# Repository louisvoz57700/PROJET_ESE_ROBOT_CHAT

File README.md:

# 🤖 PROJET_ESE_ROBOT_CHAT

Bienvenue dans le repository de notre projet de 3ème année.  
Ce projet a pour but de concevoir et développer un **robot intelligent** capable d’interagir et d’échanger de manière autonome dans le cadre du jeu "Chat".  

---

## 👥 Membres de l’équipe

- [Louis Vozzola](https://github.com/louisvoz57700)  
- [Antoine LEMARIGNIER](https://github.com/LEMARIGNIER-Antoine)  
- [Thomas TERLINDEN](https://github.com/TTrld)
- [Kenny Saint Fleur](https://github.com/Kennystflr)  

---

## 📁 Structure du projet

Ce dépôt est organisé de la manière suivante :

- `Datasheet/` : Contient les **documents techniques** des composants électroniques (datasheets, notes d’application, documents de référence).  

- `Hardware/` : Contient la **conception matérielle**, incluant les projets KiCad (schémas, PCB, librairies locales) et fichiers liés à la fabrication (impression 3D).  

- `IMG/` : Contient toutes les **images et illustrations** du projet (schémas explicatifs, rendus PCB, photos du prototype, captures pour la documentation).  

- `Software/` : Contient le **code source / firmware**, y compris les projets STM32CubeIDE, le code embarqué (C/C++) et les scripts utilitaires éventuels.

---

## 📅 Organisation

- **Phase 1 (Début Septembre)** : Étude et conception
Nous avons étudié les possibilités et choisis d'adopter [deux solutions de pcb](./Hardware).
- **Phase 2 (Mi-Septembre à Mi-Octobre)** : Développement hardware & software
Nous avons réalisé le developpement hardware du projet en 3 semaines et nous avons ensuite concentré nos efforts sur le développement des blocks individuels du software embarqué.
- **Phase 3 (Décembre)** : Intégration et tests
Nous avons intégrés et adaptés les différents blocks des capteurs et actionneurs dans le [code résultant](./Software). 
- **Phase 4  (Janvier)** : Présentation finale
Malgré le dépqart en double-dipplome de la majorité de l'équipe, nous avons travaillé a obtenir des extraits vidéos montrant le résultat de nos travaux.  

---

## 🛠️ Technologies utilisées (prévisionnel)

- **Langages** : Python / C  
- **Matériel** : STM32 / VL053 / LIDAR
- **Fabrication** : JLCPCB / Imprimante 3D FDM / Fusion 360

---
## Résultats :

### Vidéo finale du chat en jeu :
https://github.com/user-attachments/assets/e0ab9da4-8b44-4d55-9d14-98a5d518202f

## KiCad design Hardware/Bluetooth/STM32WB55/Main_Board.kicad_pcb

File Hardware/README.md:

# 🛠️ Hardware – README

Bienvenue dans ce README dédié à **l’ensemble de la partie hardware** du projet.

---

## 🧩 Architecture matérielle

Pour notre projet, nous avons conçu **deux PCB distincts**, chacun répondant à un objectif précis :

- **[Bluetooth WB55](./WB55)**  
  Carte principale intégrant le microcontrôleur **STM32WB55** et l’ensemble de la chaîne Bluetooth Low Energy.

- **[Mainboard G431](./G431)**  
  Carte secondaire conçue comme solution de secours, destinée à prendre le relais en cas de défaillance du PCB Bluetooth.

Notre stratégie de développement s’est appuyée sur la conception d’un **module Bluetooth dédié**, incluant les éléments les plus critiques du design RF, notamment l’antenne et ses réseaux d’adaptation.  
En parallèle, par souci de robustesse et de gestion des risques, une **Mainboard alternative** a été développée pour garantir la continuité du projet.

Le module Bluetooth s’étant révélé **fonctionnel et performant dès la première mise sous tension**, nous avons validé cette architecture et décidé de **ne pas retenir la solution de repli** basée sur la Mainboard.

---

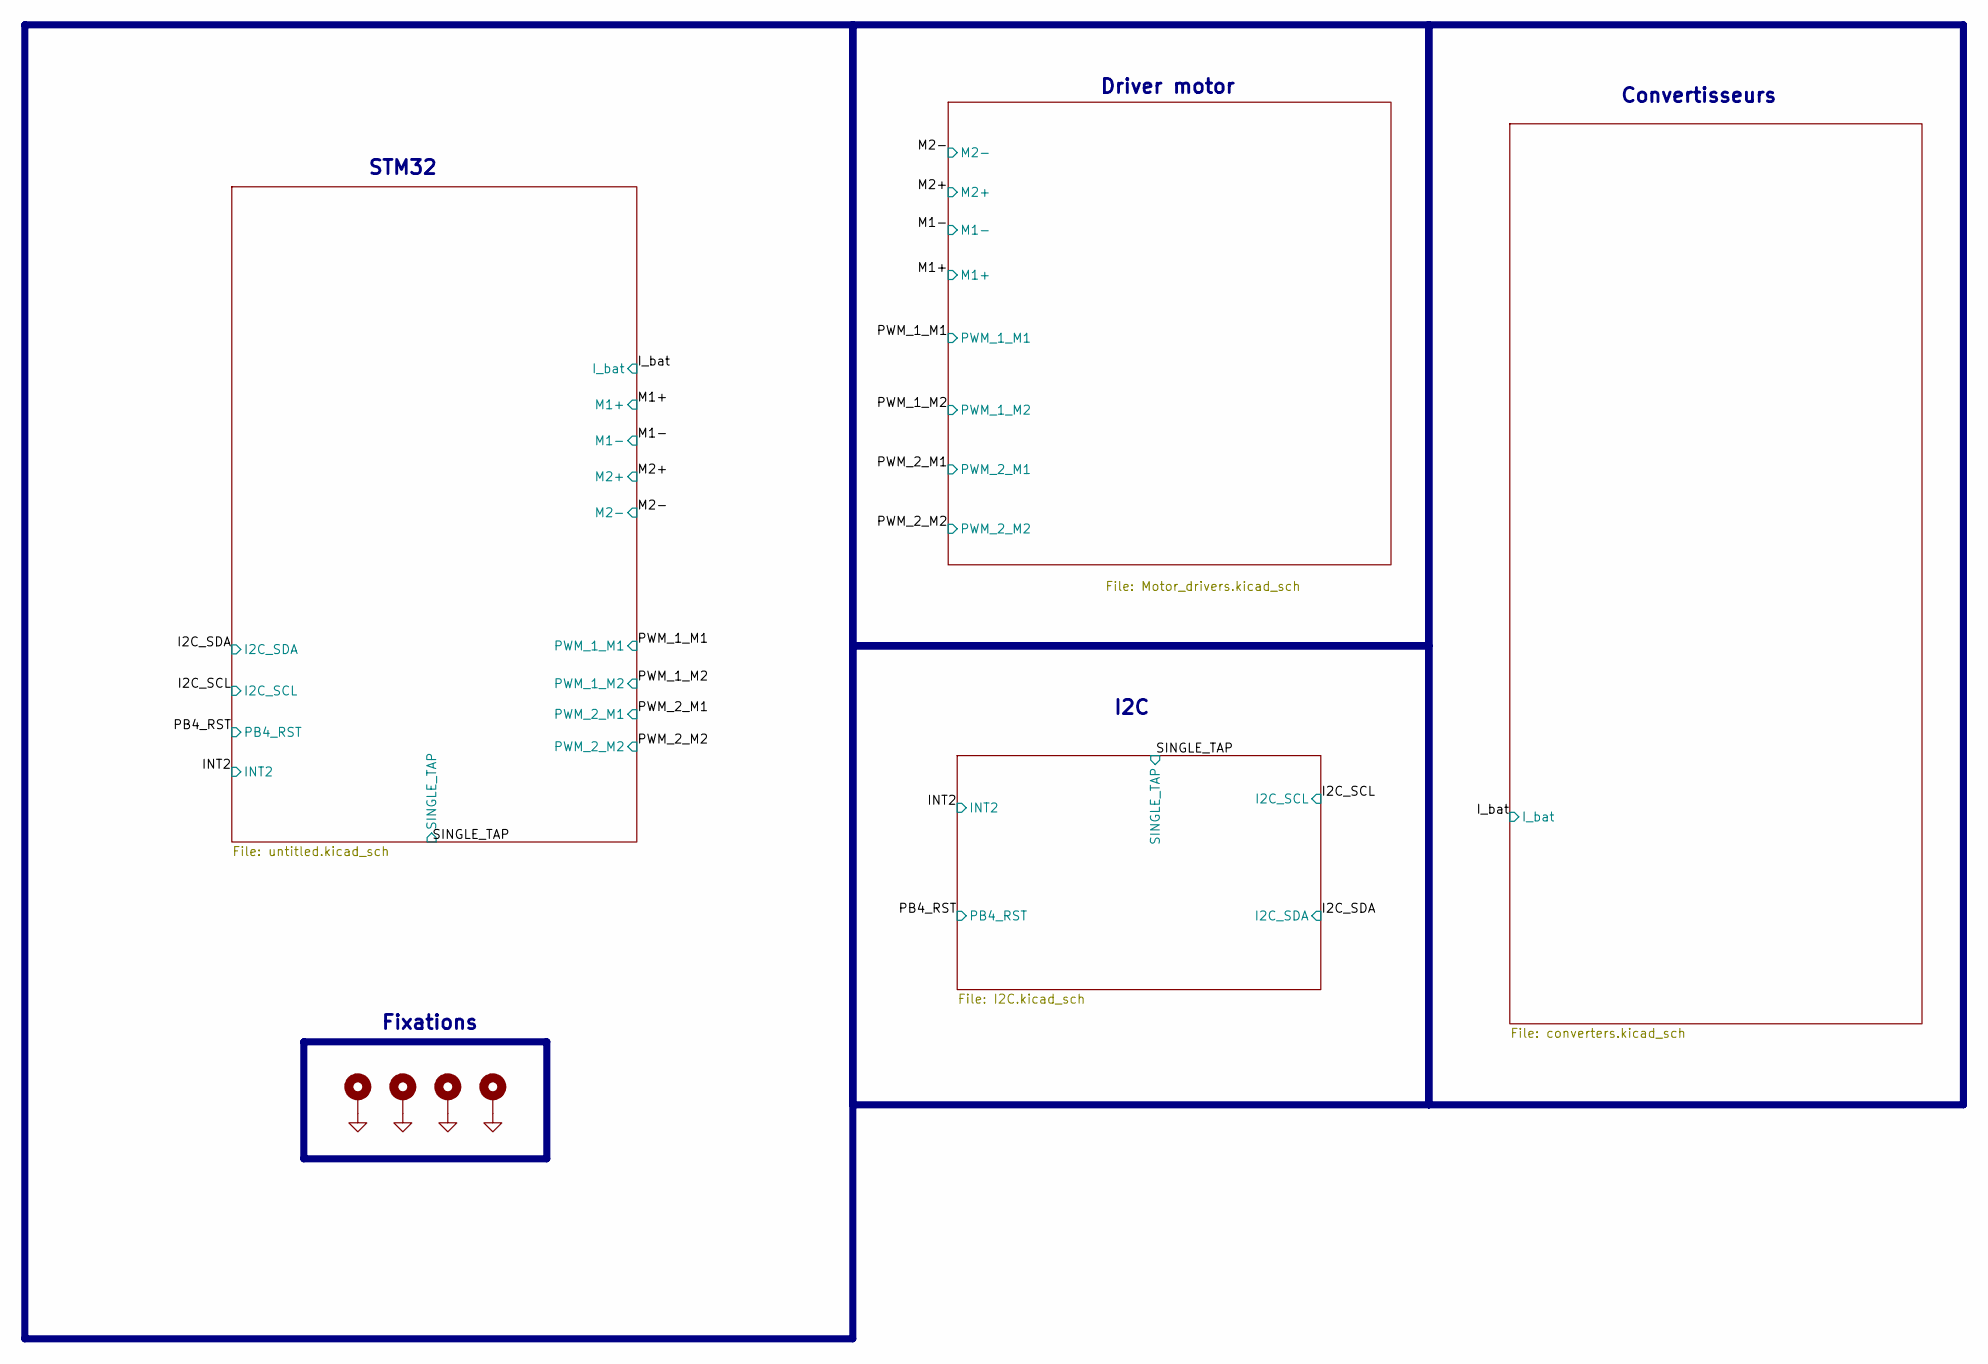
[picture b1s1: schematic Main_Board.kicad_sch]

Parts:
H1, H2, H3, H4: MountingHole_Pad; MountingHole_3.2mm_M3_Pad_Via

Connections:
GND: H1.1, H2.1, H3.1, H4.1; also elsewhere on the board

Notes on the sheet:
Convertisseurs
I2C
STM32
Fixations
Driver motor

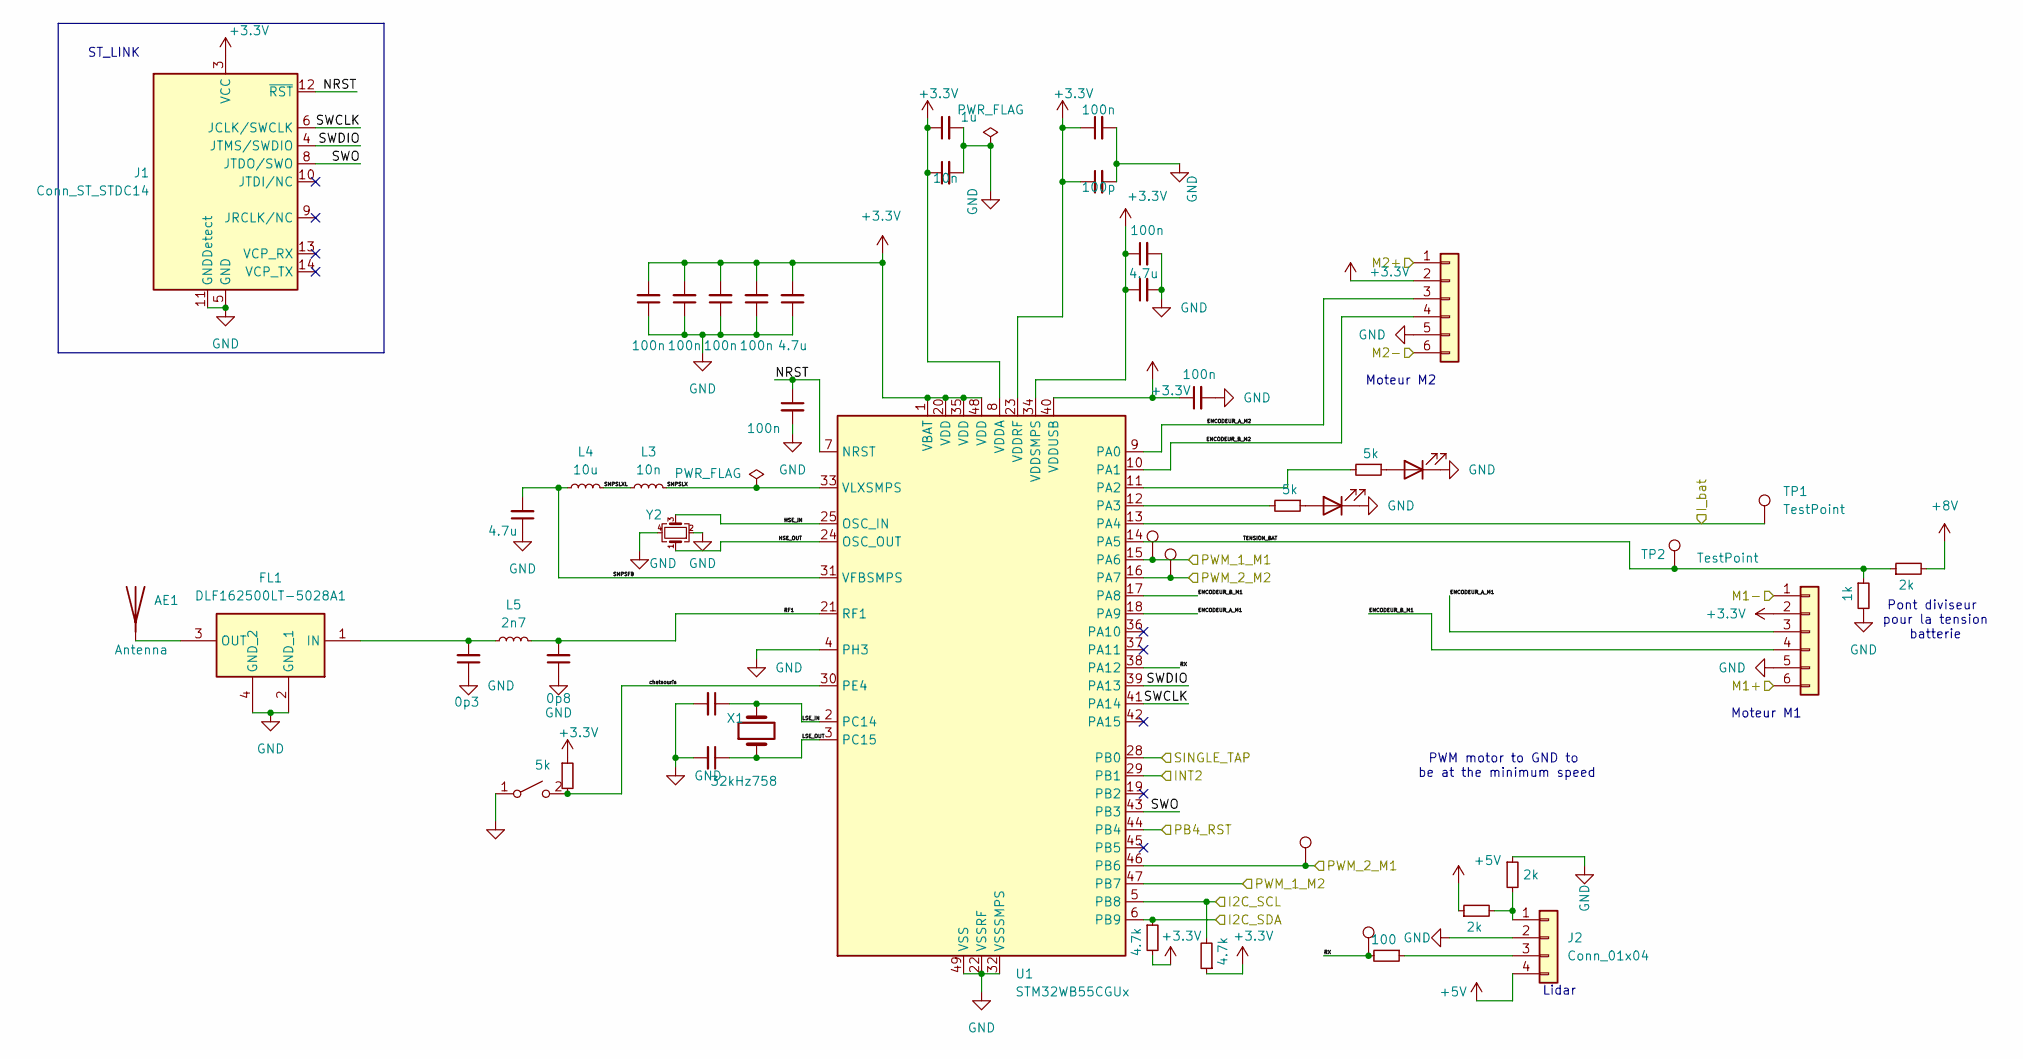
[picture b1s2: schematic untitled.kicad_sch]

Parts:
AE1: Antenna; 2.4GHz BLE
C1: 10n; C_0402_1005Metric
C2: 1u; C_0402_1005Metric
C5, C6, C7, C8, C9, C11, C38: 100n; C_0603_1608Metric
C10: 100p; C_0603_1608Metric
C12, C39, C43: 4.7u; C_0603_1608Metric
C13, C14: 13p; C_0402_1005Metric
C40: 0p3; C_0402_1005Metric
C41: 0p8; C_0402_1005Metric
C42: 100n; C_0402_1005Metric
D1, D2: LED; LED_0603_1608Metric
FL1: DLF162500LT-5028A1; DLF162500LT5028A1; Mouser Part Number 810-DLF16250LT5028A1
J1: Conn_ST_STDC14; PinHeader_2x07_P1.27mm_Vertical_SMD
J2: Conn_01x04; JST_PH_S4B-PH-K_1x04_P2.00mm_Horizontal
J11, J14: Conn_01x06; JST_PH_S6B-PH-SM4-TB_1x06-1MP_P2.00mm_Horizontal
L3: 10n; L_0402_1005Metric
L4: 10u; L_0805_2012Metric
L5: 2n7; L_0402_1005Metric
R18, R19, R24: 5k; R_0603_1608Metric
R25: 100; R_0603_1608Metric
R26, R27, R33: 2k; R_0603_1608Metric
R28, R29: 4.7k; R_0603_1608Metric
R32: 1k; R_0603_1608Metric
SW2: SW_SPST; SW_SPST_B3U-1000P-B
TP1, TP2, TP4, TP5, TP7, TP9: TestPoint; TestPoint_Pad_D1.5mm
U1: STM32WB55CGUx; QFN-48-1EP_7x7mm_P0.5mm_EP5.6x5.6mm
X1: 32kHz758; ABS06N32768kHzT
Y2: Crystal_GND24_Small; Murata 32MHz

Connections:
+3.3V: C1.1, C2.1, C5.2, C6.2, C7.2, C8.2, C9.1, C10.1, C11.1, C12.1, C38.1, C43.2, J1.3 (VCC), J11.2, J14.2, R24.1, R28.2, R29.1, U1.1 (VBAT), U1.8 (VDDA), U1.20 (VDD), U1.23 (VDDRF), U1.34 (VDDSMPS), U1.35 (VDD), U1.40 (VDDUSB), U1.48 (VDD); also elsewhere on the board
+5V: J2.4, R27.1; also elsewhere on the board
+8V: R33.2; also elsewhere on the board
/I2C_SCL: R29.2, U1.5 (PB8); also elsewhere on the board
/I2C_SDA: R28.1, U1.6 (PB9); also elsewhere on the board
/INT2: U1.29 (PB1); also elsewhere on the board
/I_bat: TP1.1, U1.13 (PA4); also elsewhere on the board
/M1+: J11.6; also elsewhere on the board
/M1-: J11.1; also elsewhere on the board
/M2+: J14.1; also elsewhere on the board
/M2-: J14.6; also elsewhere on the board
/PB4_RST: U1.44 (PB4); also elsewhere on the board
/PWM_1_M1: TP4.1, U1.15 (PA6); also elsewhere on the board
/PWM_1_M2: U1.47 (PB7); also elsewhere on the board
/PWM_2_M1: TP9.1, U1.46 (PB6); also elsewhere on the board
/PWM_2_M2: TP5.1, U1.16 (PA7); also elsewhere on the board
/SINGLE_TAP: U1.28 (PB0); also elsewhere on the board
/STM32/ENCODEUR_A_M1: J11.3, U1.18 (PA9)
/STM32/ENCODEUR_A_M2: J14.3, U1.9 (PA0)
/STM32/ENCODEUR_B_M1: J11.4, U1.17 (PA8)
/STM32/ENCODEUR_B_M2: J14.4, U1.10 (PA1)
/STM32/HSE_IN: U1.25 (OSC_IN), Y2.3
/STM32/HSE_OUT: U1.24 (OSC_OUT), Y2.1
/STM32/LSE_IN: C13.1, U1.2 (PC14), X1.2
/STM32/LSE_OUT: C14.1, U1.3 (PC15), X1.1
/STM32/NRST: C42.1, J1.12 (~RST), U1.7 (NRST)
/STM32/RF1: C41.2, L5.2, U1.21 (RF1)
/STM32/RX: R25.2, TP7.1, U1.38 (PA12)
/STM32/SMPSFB: C39.2, L4.1, U1.31 (VFBSMPS)
/STM32/SMPSLX: L3.2, U1.33 (VLXSMPS)
/STM32/SMPSLXL: L3.1, L4.2
/STM32/SWCLK: J1.6 (JCLK/SWCLK), U1.41 (PA14)
/STM32/SWDIO: J1.4 (JTMS/SWDIO), U1.39 (PA13)
/STM32/SWO: J1.8 (JTDO/SWO), U1.43 (PB3)
/STM32/TENSION_BAT: R32.1, R33.1, TP2.1, U1.14 (PA5)
/STM32/chatsouris: R24.2, SW2.2 (B), U1.30 (PE4)
GND: C1.2, C2.2, C5.1, C6.1, C7.1, C8.1, C9.2, C10.2, C11.2, C12.2, C13.2, C14.2, C38.2, C39.1, C40.1, C41.1, C42.2, C43.1, D1.1 (K), D2.1 (K), FL1.2 (GND_1), FL1.4 (GND_2), J1.5 (GND), J1.7 (GND), J1.11 (GNDDetect), J2.2, J11.5, J14.5, R26.1, R32.2, SW2.1 (A), U1.4 (PH3), U1.22 (VSSRF), U1.32 (VSSSMPS), U1.49 (VSS), Y2.2, Y2.4; also elsewhere on the board
unnamed: AE1.1 (A), FL1.3 (OUT)
unnamed: D1.2 (A), R18.1
unnamed: D2.2 (A), R19.1
unnamed: C40.2, FL1.1 (IN), L5.1
unnamed: J2.1, R26.2, R27.2
unnamed: J2.3, R25.1
unnamed: R18.2, U1.11 (PA2)
unnamed: R19.2, U1.12 (PA3)

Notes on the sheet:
Pont diviseur pour la tension batterie
Moteur M2
Moteur M1
ST_LINK
Lidar
PWM motor to GND to be at the minimum speed

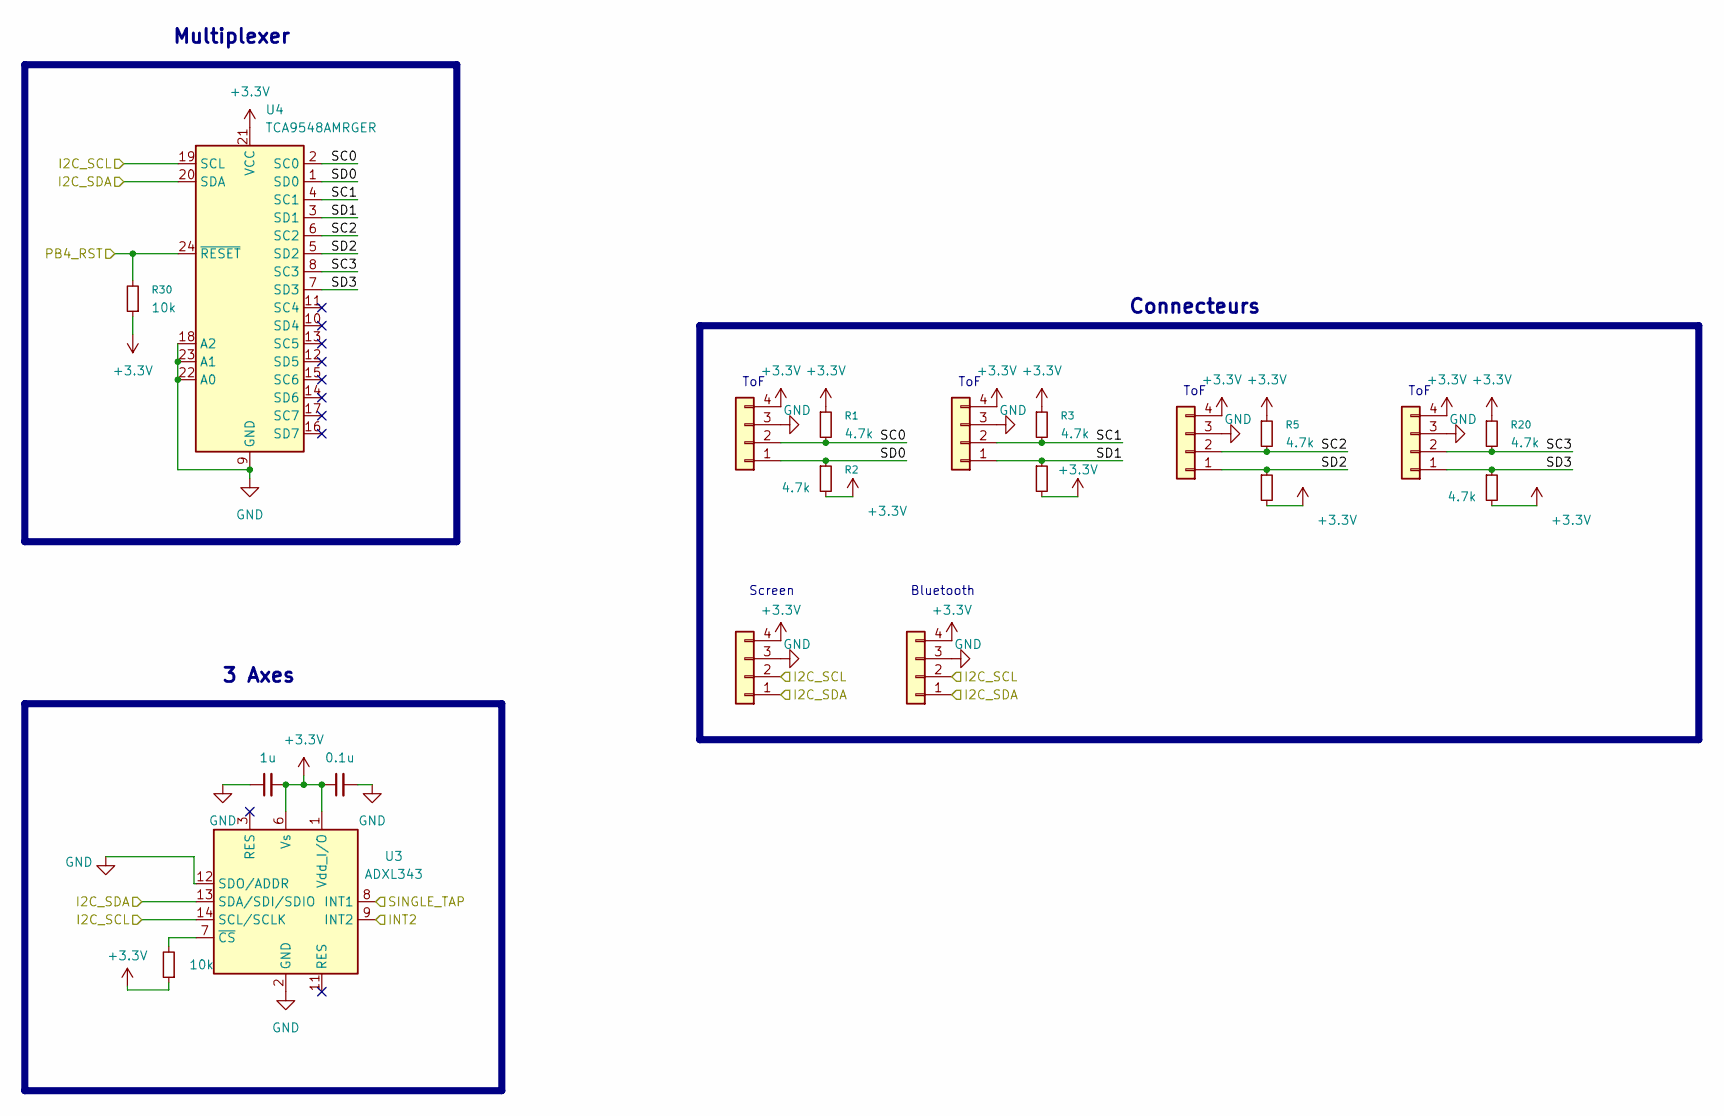
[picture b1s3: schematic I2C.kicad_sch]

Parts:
C36: 0.1u; C_0603_1608Metric
C37: 1u; C_0603_1608Metric
J3, J4, J5, J6, J7, J8: Conn_01x04; JST_PH_B4B-PH-K_1x04_P2.00mm_Vertical
R1, R2, R3, R4, R5, R6, R20, R21: 4.7k; R_0603_1608Metric
R30, R31: 10k; R_0603_1608Metric
U3: ADXL343; LGA-14_3x5mm_P0.8mm_LayoutBorder1x6y
U4: TCA9548AMRGER; Texas_RGE0024C_VQFN-24-1EP_4x4mm_P0.5mm_EP2.1x2.1mm

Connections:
+3.3V: C36.1, C37.2, J3.4, J4.4, J5.4, J6.4, J7.4, J8.4, R1.1, R2.2, R3.1, R4.2, R5.1, R6.2, R20.1, R21.2, R30.1, R31.1, U3.1 (Vdd_I/O), U3.6 (Vs), U4.21 (VCC); also elsewhere on the board
/I2C/SC0: J3.2, R1.2, U4.2 (SC0)
/I2C/SC1: J4.2, R3.2, U4.4 (SC1)
/I2C/SC2: J5.2, R5.2, U4.6 (SC2)
/I2C/SC3: J6.2, R20.2, U4.8 (SC3)
/I2C/SD0: J3.1, R2.1, U4.1 (SD0)
/I2C/SD1: J4.1, R4.1, U4.3 (SD1)
/I2C/SD2: J5.1, R6.1, U4.5 (SD2)
/I2C/SD3: J6.1, R21.1, U4.7 (SD3)
/I2C_SCL: J7.2, J8.2, U3.14 (SCL/SCLK), U4.19 (SCL); also elsewhere on the board
/I2C_SDA: J7.1, J8.1, U3.13 (SDA/SDI/SDIO), U4.20 (SDA); also elsewhere on the board
/INT2: U3.9 (INT2); also elsewhere on the board
/PB4_RST: R30.2, U4.24 (~RESET); also elsewhere on the board
/SINGLE_TAP: U3.8 (INT1); also elsewhere on the board
GND: C36.2, C37.1, J3.3, J4.3, J5.3, J6.3, J7.3, J8.3, U3.2 (GND), U3.4 (GND), U3.5 (GND), U3.12 (SDO/ADDR), U4.9 (GND), U4.18 (A2), U4.22 (A0), U4.23 (A1); also elsewhere on the board
unnamed: R31.2, U3.7 (~CS)

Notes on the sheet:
Screen
ToF
3 Axes
Bluetooth
Multiplexer
Connecteurs

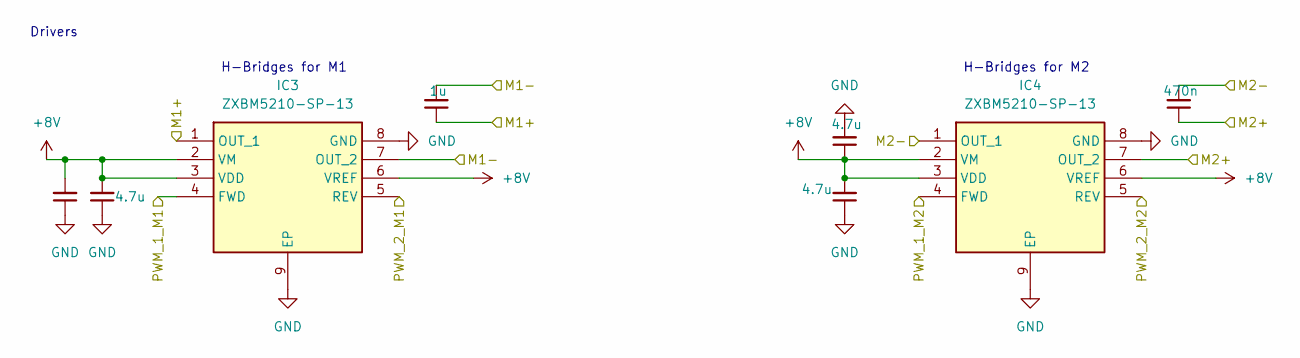
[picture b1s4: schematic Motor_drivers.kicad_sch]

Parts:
C29, C30, C32, C33: 4.7u; C_0603_1608Metric
C31: 1u; C_0603_1608Metric
C34: 470n; C_0603_1608Metric
IC3, IC4: ZXBM5210-SP-13; Diodes_SO-8EP; Mouser Part Number 621-ZXBM5210-SP-13

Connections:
+8V: C29.2, C30.2, C32.1, C33.2, IC3.2 (VM), IC3.3 (VDD), IC3.6 (VREF), IC4.2 (VM), IC4.3 (VDD), IC4.6 (VREF); also elsewhere on the board
/M1+: C31.1, IC3.1 (OUT_1); also elsewhere on the board
/M1-: C31.2, IC3.7 (OUT_2); also elsewhere on the board
/M2+: C34.1, IC4.7 (OUT_2); also elsewhere on the board
/M2-: C34.2, IC4.1 (OUT_1); also elsewhere on the board
/PWM_1_M1: IC3.4 (FWD); also elsewhere on the board
/PWM_1_M2: IC4.4 (FWD); also elsewhere on the board
/PWM_2_M1: IC3.5 (REV); also elsewhere on the board
/PWM_2_M2: IC4.5 (REV); also elsewhere on the board
GND: C29.1, C30.1, C32.2, C33.1, IC3.8 (GND), IC3.9 (EP), IC4.8 (GND), IC4.9 (EP); also elsewhere on the board

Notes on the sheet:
Drivers
H-Bridges for M1
H-Bridges for M2

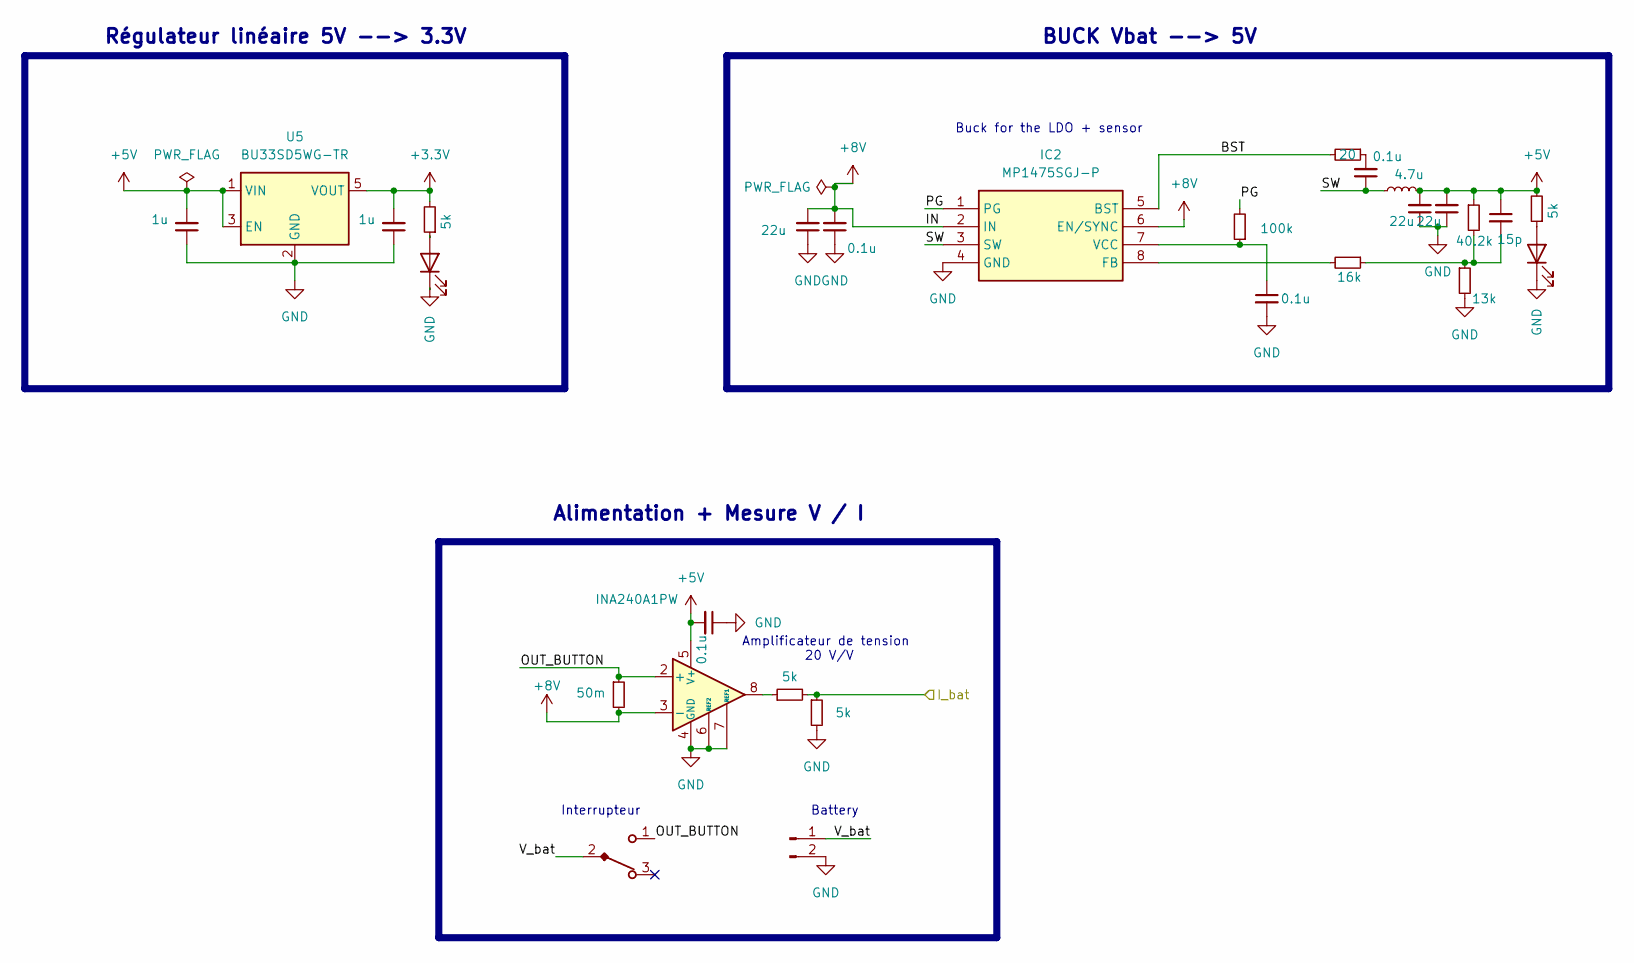
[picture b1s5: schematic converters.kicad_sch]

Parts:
C15, C16: 1u; C_0603_1608Metric
C21, C23, C27: 22u; C_0603_1608Metric
C22, C24, C25, C35: 0.1u; C_0603_1608Metric
C28: 15p; C_0603_1608Metric
D3, D4: LED; LED_0603_1608Metric
IC2: MP1475SGJ-P; TSOT 23-8; Mouser Part Number 946-MP1475SGJ-P
J9: Conn_01x02_Pin; JST_XH_B2B-XH-A_1x02_P2.50mm_Vertical
L2: 4.7u; 74404054068
R8: 20; R_0603_1608Metric
R9: 16k; R_0603_1608Metric
R10: 40.2k; R_0603_1608Metric
R11: 13k; R_0603_1608Metric
R12: 100k; R_0603_1608Metric
R15: 50m; R_6431
R16, R17, R22, R23: 5k; R_0603_1608Metric
SW1: SW_Wurth; SW_Wurth_WS-TOTV_472121020311; Part Number 472121010111
U2: INA240A1PW; TSSOP-8_4.4x3mm_P0.65mm
U5: BU33SD5WG-TR; SSOP-5

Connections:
+3.3V: C16.2, R22.2, U5.5 (VOUT); also elsewhere on the board
+5V: C15.2, C23.2, C27.2, C28.1, C35.2, L2.2, R10.1, R23.2, U2.5 (V+), U5.1 (VIN), U5.3 (EN); also elsewhere on the board
+8V: C21.2, C25.2, IC2.2 (IN), IC2.6 (EN/SYNC), R15.2, U2.3 (-); also elsewhere on the board
/Converters/BST: IC2.5 (BST), R8.2
/Converters/OUT_BUTTON: R15.1, SW1.1, U2.2 (+)
/Converters/PG: IC2.1 (PG), R12.2
/Converters/SW: C22.1, IC2.3 (SW), L2.1
/Converters/V_bat: J9.1, SW1.2
/I_bat: R16.1, R17.2; also elsewhere on the board
GND: C15.1, C16.1, C21.1, C23.1, C24.2, C25.1, C27.1, C35.1, D3.1 (K), D4.1 (K), IC2.4 (GND), J9.2, R11.2, R16.2, U2.1 (GND), U2.4 (GND), U2.6 (REF2), U2.7 (REF1), U5.2 (GND); also elsewhere on the board
unnamed: C22.2, R8.1
unnamed: C28.2, R9.1, R10.2, R11.1
unnamed: D3.2 (A), R22.1
unnamed: D4.2 (A), R23.1
unnamed: IC2.8 (FB), R9.2
unnamed: C24.1, IC2.7 (VCC), R12.1
unnamed: R17.1, U2.8

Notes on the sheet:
Battery
Buck for the LDO + sensor
BUCK Vbat --> 5V
Interrupteur
Alimentation + Mesure V / I
Amplificateur de tension 20 V/V
Régulateur linéaire 5V --> 3.3V

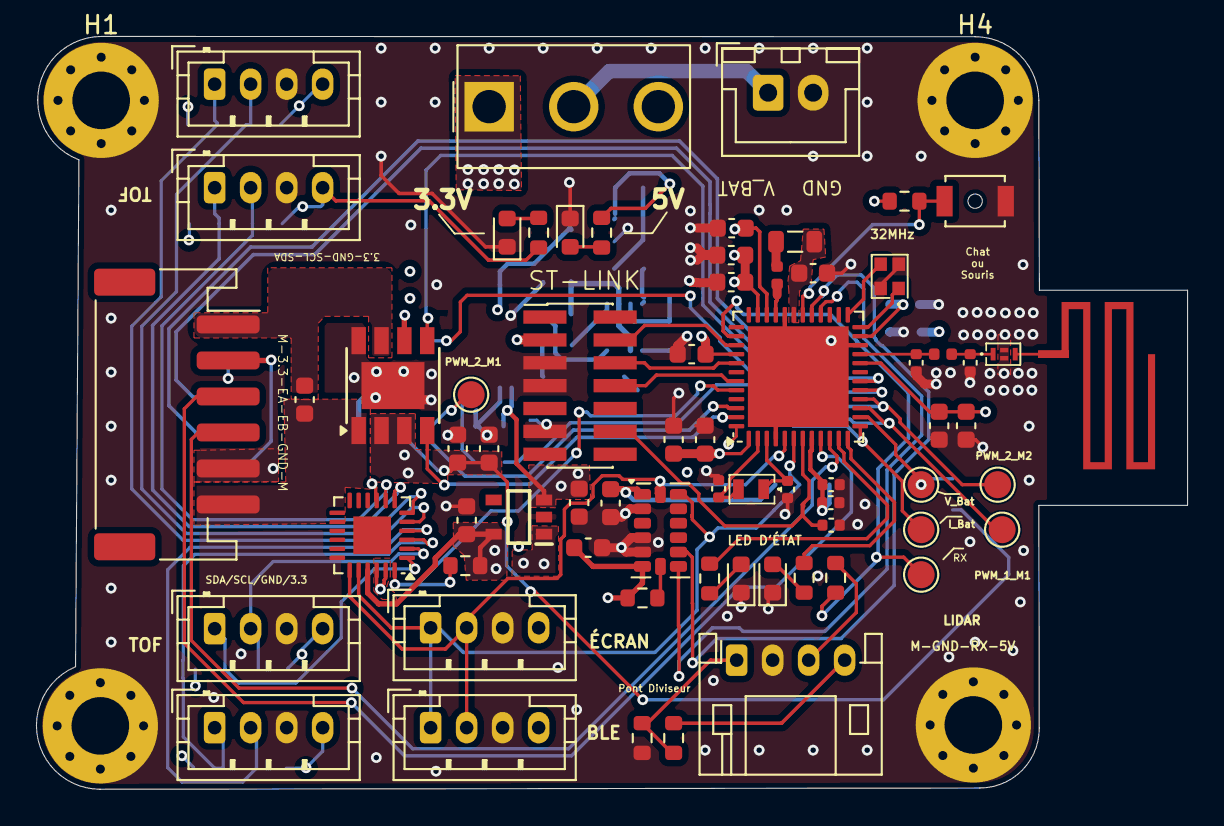
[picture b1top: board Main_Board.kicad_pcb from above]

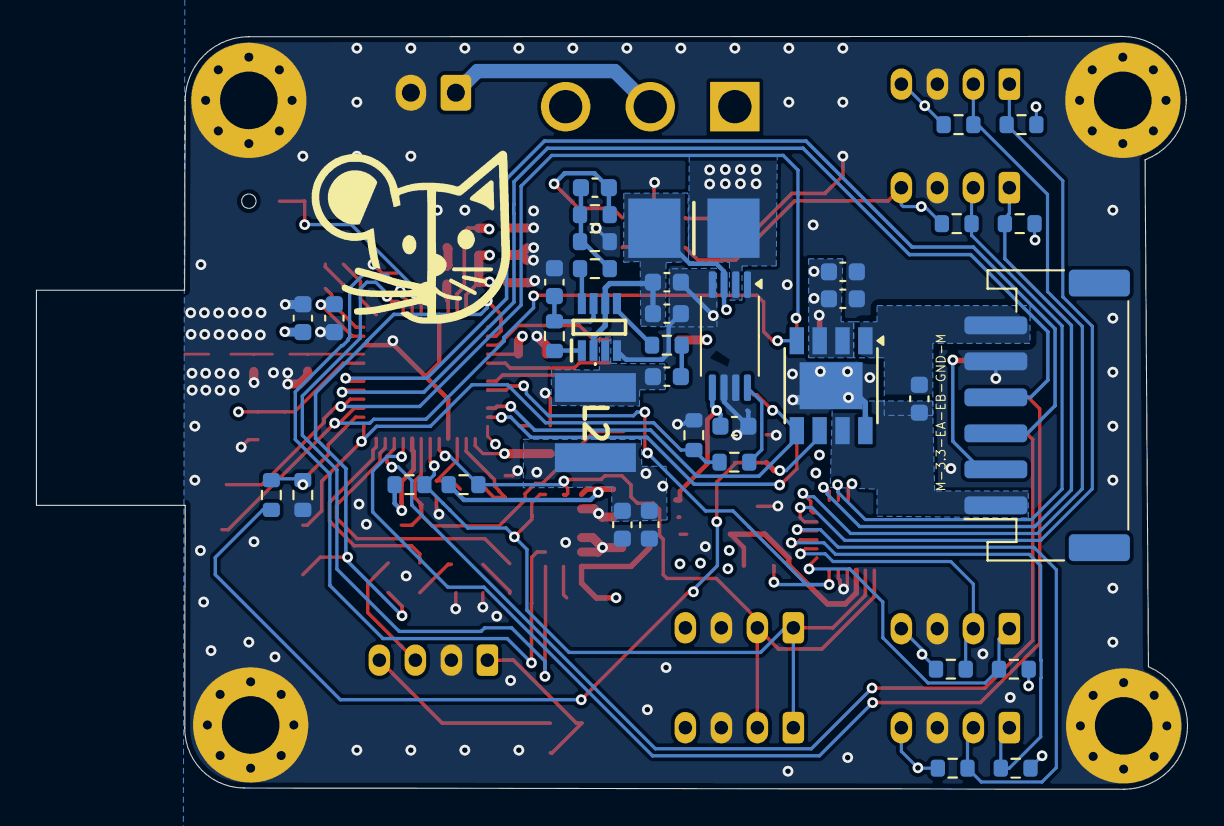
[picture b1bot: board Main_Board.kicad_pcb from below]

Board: 4 copper layers, 64.0 x 41.8 mm, 109 parts (38 on the bottom side), 66 nets.

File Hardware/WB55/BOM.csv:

"Id";"Designator";"Footprint";"Quantity";"Designation";"Supplier and ref";
1;"C43,C33,C32,C39,C12,C29,C30";"C_0603_1608Metric";7;"4.7u";;;
2;"J2";"JST_PH_S4B-PH-K_1x04_P2.00mm_Horizontal";1;"Conn_01x04";;;
3;"AE1";"2.4GHz BLE";1;"Antenna";;;
4;"J14,J11";"JST_PH_S6B-PH-SM4-TB_1x06-1MP_P2.00mm_Horizontal";2;"Conn_01x06";;;
5;"SW2";"SW_SPST_B3U-1000P-B";1;"SW_SPST";;;
6;"C1";"C_0402_1005Metric";1;"10n";;;
7;"R19,R22,R23,R18,R24,R16,R17";"R_0603_1608Metric";7;"5k";;;
8;"C40";"C_0402_1005Metric";1;"0p3";;;
9;"C13,C14";"C_0402_1005Metric";2;"13p";;;
10;"U4";"Texas_RGE0024C_VQFN-24-1EP_4x4mm_P0.5mm_EP2.1x2.1mm";1;"TCA9548AMRGER";;;
11;"C15,C16,C37,C31";"C_0603_1608Metric";4;"1u";;;
12;"TP7,TP9,TP2,TP4,TP1,TP5";"TestPoint_Pad_D1.5mm";6;"TestPoint";;;
13;"C41";"C_0402_1005Metric";1;"0p8";;;
14;"J9";"JST_XH_B2B-XH-A_1x02_P2.50mm_Vertical";1;"Conn_01x02_Pin";;;
15;"J4,J3,J8,J5,J7,J6";"JST_PH_B4B-PH-K_1x04_P2.00mm_Vertical";6;"Conn_01x04";;;
16;"D2,D1,D4,D3";"LED_0603_1608Metric";4;"LED";;;
17;"L3";"L_0402_1005Metric";1;"10n";;;
18;"R26,R27,R33";"R_0603_1608Metric";3;"2k";;;
19;"C8,C38,C6,C7,C11,C5,C9";"C_0603_1608Metric";7;"100n";;;
20;"C2";"C_0402_1005Metric";1;"1u";;;
21;"J1";"PinHeader_2x07_P1.27mm_Vertical_SMD";1;"Conn_ST_STDC14";;;
22;"IC4,IC3";"Diodes_SO-8EP";2;"ZXBM5210-SP-13";;;
23;"U5";"SSOP-5";1;"BU33SD5WG-TR";;;
24;"FL1";"DLF162500LT5028A1";1;"DLF162500LT-5028A1";;;
25;"R31,R30";"R_0603_1608Metric";2;"10k";;;
26;"U1";"QFN-48-1EP_7x7mm_P0.5mm_EP5.6x5.6mm";1;"STM32WB55CGUx";;;
27;"R25";"R_0603_1608Metric";1;"100";;;
28;"Y2";"Murata 32MHz";1;"Crystal_GND24_Small";;;
29;"C34";"C_0603_1608Metric";1;"470n";;;
30;"C42";"C_0402_1005Metric";1;"100n";;;
31;"L5";"L_0402_1005Metric";1;"2n7";;;
32;"U3";"LGA-14_3x5mm_P0.8mm_LayoutBorder1x6y";1;"ADXL343";;;
33;"X1";"ABS06N32768kHzT";1;"32kHz758";;;
34;"SW1";"SW_Wurth_WS-TOTV_472121020311";1;"SW_Wurth";;;
35;"L4";"L_0805_2012Metric";1;"10u";;;
36;"C36,C24,C22,C35,C25";"C_0603_1608Metric";5;"0.1u";;;
37;"C28";"C_0603_1608Metric";1;"15p";;;
38;"L2";"74404054068";1;"4.7u";;;
39;"R11";"R_0603_1608Metric";1;"13k";;;
40;"R9";"R_0603_1608Metric";1;"16k";;;
41;"R2,R3,R21,R1,R5,R20,R4,R28,R6,R29";"R_0603_1608Metric";10;"4.7k";;;
42;"C23,C21,C27";"C_0603_1608Metric";3;"22u";;;
43;"R12";"R_0603_1608Metric";1;"100k";;;
44;"C10";"C_0603_1608Metric";1;"100p";;;
45;"U2";"TSSOP-8_4.4x3mm_P0.65mm";1;"INA240A1PW";;;
46;"IC2";"TSOT 23-8";1;"MP1475SGJ-P";;;
47;"R15";"R_6431";1;"50m";;;
48;"R10";"R_0603_1608Metric";1;"40.2k";;;
49;"R32";"R_0603_1608Metric";1;"1k";;;
50;"R8";"R_0603_1608Metric";1;"20";;;

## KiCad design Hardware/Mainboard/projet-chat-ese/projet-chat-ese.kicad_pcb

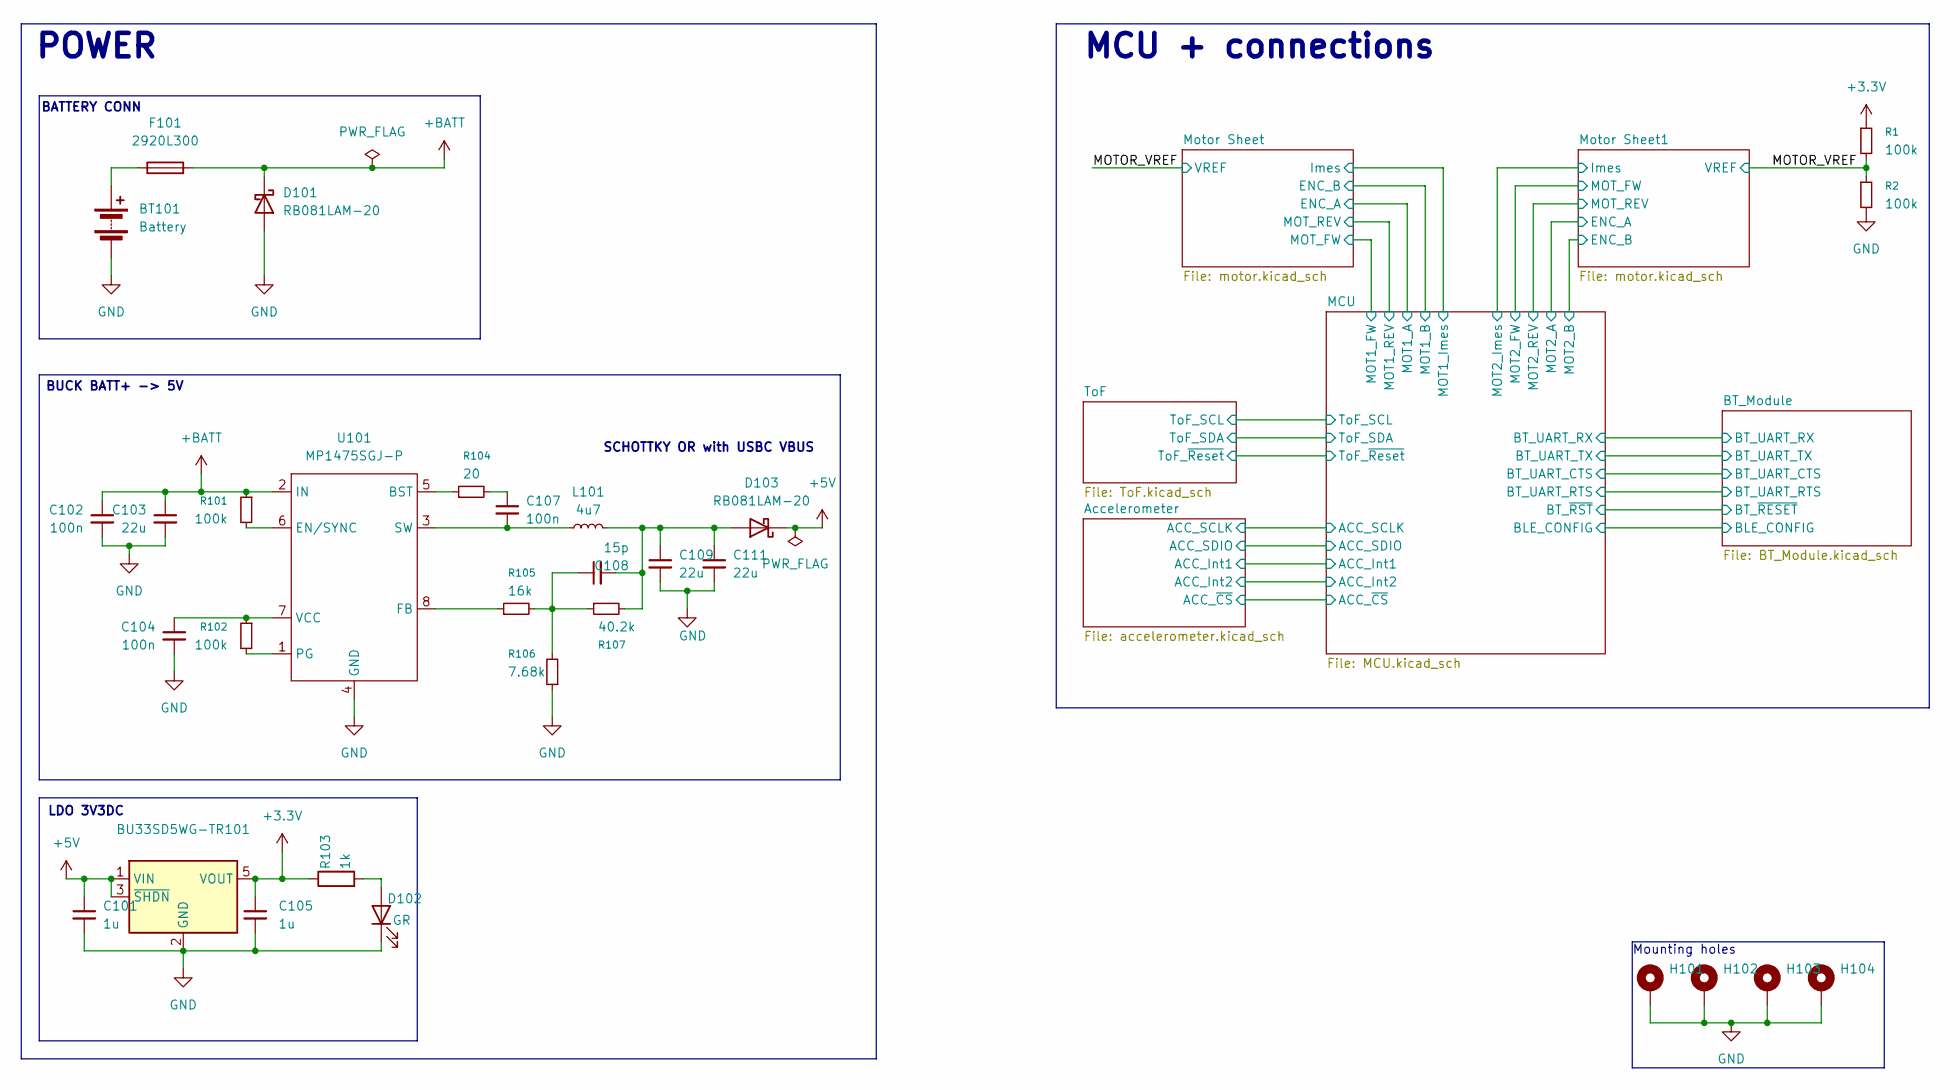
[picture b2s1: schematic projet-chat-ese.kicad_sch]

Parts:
BT101: Battery; JST_XH_B2B-XH-AM_1x02_P2.50mm_Vertical
BU33SD5WG-TR101: LM1117DT-3.3; SOT-23-5
C101, C105: 1u; C_0603_1608Metric_Pad1.08x0.95mm_HandSolder
C102, C104, C107: 100n; C_0402_1005Metric
C103, C109, C111: 22u; C_0805_2012Metric
C108: 15p; C_0402_1005Metric
D101, D103: RB081LAM-20; D_SOD-128
D102: GR; LED_0603_1608Metric
F101: 2920L300
H101, H102, H103, H104: MountingHole_Pad; MountingHole_3.2mm_M3_DIN965_Pad_TopBottom
L101: 4u7; L_APV_ANR5020
R1, R2, R101, R102: 100k; R_0402_1005Metric
R103: 1k; R_0402_1005Metric
R104: 20; R_0402_1005Metric
R105: 16k; R_0402_1005Metric
R106: 7.68k; R_0402_1005Metric
R107: 40.2k; R_0402_1005Metric
U101: MP1475SGJ-P; TSOT-23-8; MPN MP1475SGJ-P

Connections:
+5V: BU33SD5WG-TR101.1 (VIN), BU33SD5WG-TR101.3 (~SHDN), C101.1, D103.1 (K); also elsewhere on the board
+BATT: C102.1, C103.1, D101.1 (K), F101.2, R101.1, U101.2 (IN); also elsewhere on the board
/MOTOR_VREF: R1.2, R2.1; also elsewhere on the board
GND: BT101.1 (-), BU33SD5WG-TR101.2 (GND), C101.2, C102.2, C103.2, C104.2, C105.2, C109.2, C111.2, D101.2 (A), D102.1 (K), H101.1, H102.1, H103.1, H104.1, R2.2, R106.1, U101.4 (GND); also elsewhere on the board
unnamed: BT101.2 (+), F101.1
unnamed: C107.1, R104.2
unnamed: C108.1, R105.2, R106.2, R107.1
unnamed: D102.2 (A), R103.2
unnamed: C108.2, C109.1, C111.1, D103.2 (A), L101.1, R107.2
unnamed: R104.1, U101.5 (BST)
unnamed: R101.2, U101.6 (EN/SYNC)
unnamed: R105.1, U101.8 (FB)
unnamed: R102.2, U101.1 (PG)
unnamed: C107.2, L101.2, U101.3 (SW)
unnamed: C104.1, R102.1, U101.7 (VCC)

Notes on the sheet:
Mounting holes
LDO 3V3DC
MCU + connections
BATTERY CONN
SCHOTTKY OR with USBC VBUS
POWER
BUCK BATT+ -> 5V
